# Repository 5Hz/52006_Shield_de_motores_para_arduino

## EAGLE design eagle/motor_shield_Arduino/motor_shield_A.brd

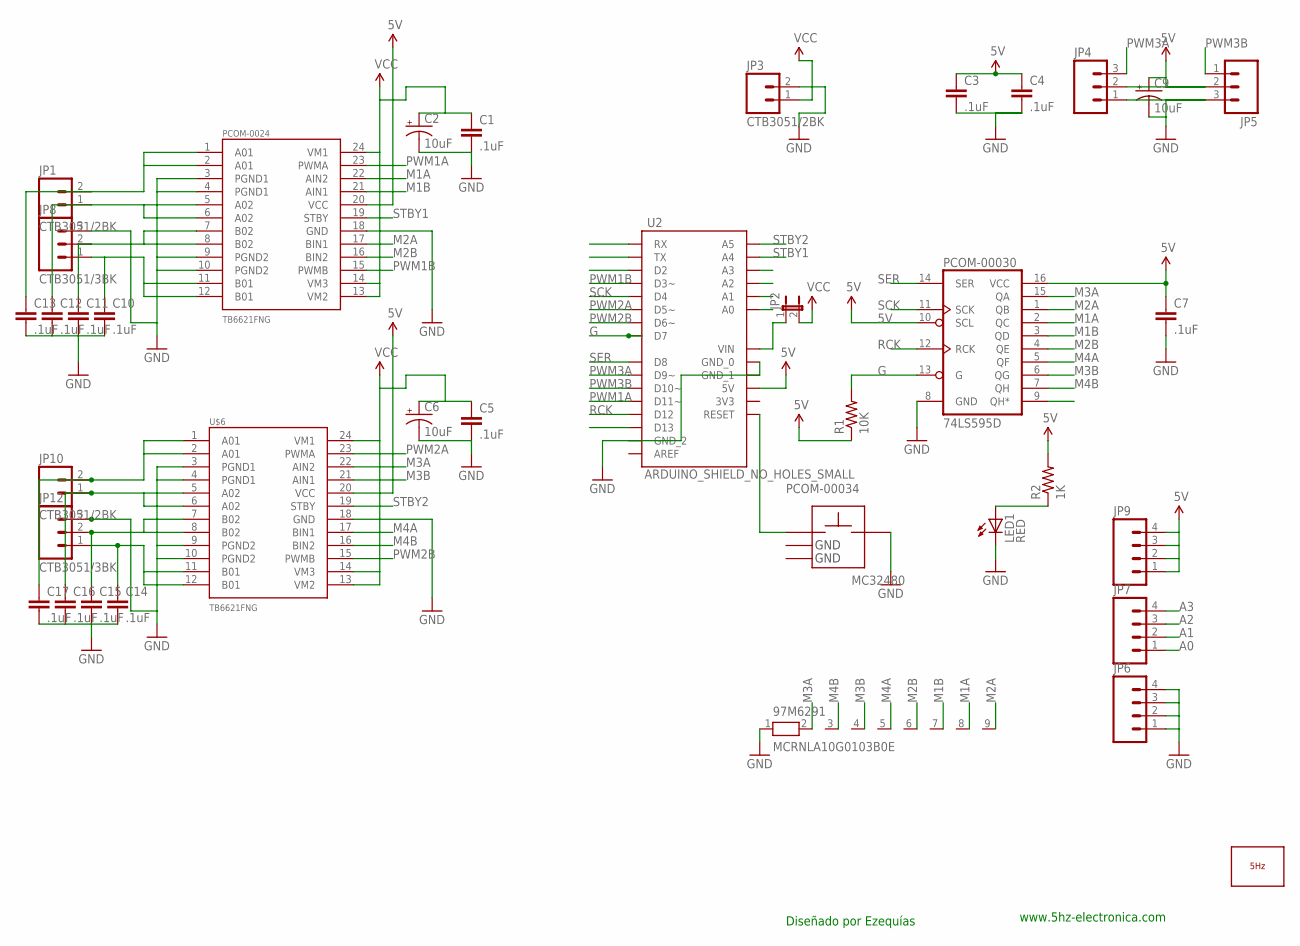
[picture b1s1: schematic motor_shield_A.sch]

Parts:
97M6291: MCRNLA10G0103B0E; RN-9
C1, C3, C4, C5, C7, C10, C11, C12, C13, C14, C15, C16, C17: .1uF; 0603-CAP
C2, C6: 10uF; EIA3528-KIT
C9: 10uF; EIA3216
JP1, JP3, JP10: CTB3051/2BK; SCREWTERMINAL-3.5MM-2
JP2: JUMPER-2PTH; 1X02
JP4, JP5: M03PTH; 1X03
JP6, JP7, JP9: M04PTH; 1X04
JP8, JP12: CTB3051/3BK; SCREWTERMINAL-3.5MM-3
LED1: RED; LED-0603
LOGO1: LOGO_5HZ_H_COOPER_10MM; 5HZ_LOGO_H_COOPER_10MM
PCOM-0024: TB6621FNG; SSOP24
PCOM-00030: 74LS595D; SO16
PCOM-00034: MC32480; MC32840
R1: 10K; 0603-RES
R2: 1K; 0603-RES
U2: ARDUINO_SHIELD_NO_HOLES_SMALL; UNO_SHIELD_SMALL_NO_HOLES
U$6: TB6621FNG; SSOP24

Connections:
5V: C3.1, C4.1, C7.1, C9.A (+), JP4.2, JP5.2, JP9.1, JP9.2, JP9.3, JP9.4, PCOM-0024.20 (VCC), PCOM-00030.10 (SCL), PCOM-00030.16 (VCC), R1.1, R2.2, U2.5V, U$6.20 (VCC)
A0: JP7.1, U2.A0
A1: JP7.2, U2.A1
A2: JP7.3, U2.A2
A3: JP7.4, U2.A3
G: PCOM-00030.13 (G), R1.2, U2.D7
GND: 97M6291.1, C1.2, C2.C (-), C3.2, C4.2, C5.2, C6.C (-), C7.2, C9.C (-), C10.2, C11.2, C12.2, C13.2, C14.2, C15.2, C16.2, C17.2, JP3.2, JP4.1, JP5.3, JP6.1, JP6.2, JP6.3, JP6.4, JP8.3, JP12.3, LED1.C, PCOM-0024.3 (PGND1), PCOM-0024.4 (PGND1), PCOM-0024.9 (PGND2), PCOM-0024.10 (PGND2), PCOM-0024.18 (GND), PCOM-00030.8 (GND), PCOM-00034.B, U2.GND_0, U2.GND_1, U2.GND_2, U$6.3 (PGND1), U$6.4 (PGND1), U$6.9 (PGND2), U$6.10 (PGND2), U$6.18 (GND)
M1A: 97M6291.8, PCOM-0024.22 (AIN2), PCOM-00030.2 (QC)
M1B: 97M6291.7, PCOM-0024.21 (AIN1), PCOM-00030.3 (QD)
M2A: 97M6291.9, PCOM-0024.17 (BIN1), PCOM-00030.1 (QB)
M2B: 97M6291.6, PCOM-0024.16 (BIN2), PCOM-00030.4 (QE)
M3A: 97M6291.2, PCOM-00030.15 (QA), U$6.22 (AIN2)
M3B: 97M6291.4, PCOM-00030.6 (QG), U$6.21 (AIN1)
M4A: 97M6291.5, PCOM-00030.5 (QF), U$6.17 (BIN1)
M4B: 97M6291.3, PCOM-00030.7 (QH), U$6.16 (BIN2)
unnamed: C13.1, JP1.2, PCOM-0024.1 (A01), PCOM-0024.2 (A01)
unnamed: C15.1, JP12.2, U$6.7 (B02), U$6.8 (B02)
unnamed: C12.1, JP1.1, PCOM-0024.5 (A02), PCOM-0024.6 (A02)
unnamed: C14.1, JP12.1, U$6.11 (B01), U$6.12 (B01)
unnamed: C11.1, JP8.2, PCOM-0024.7 (B02), PCOM-0024.8 (B02)
unnamed: JP2.1, U2.VIN
unnamed: C10.1, JP8.1, PCOM-0024.11 (B01), PCOM-0024.12 (B01)
unnamed: PCOM-00034.A@1 (A), U2.RES (RESET)
unnamed: LED1.A, R2.1
unnamed: C17.1, JP10.2, U$6.1 (A01), U$6.2 (A01)
unnamed: C16.1, JP10.1, U$6.5 (A02), U$6.6 (A02)
PWM1A: PCOM-0024.23 (PWMA), U2.D11 (D11~)
PWM1B: PCOM-0024.15 (PWMB), U2.D3 (D3~)
PWM2A: U2.D5 (D5~), U$6.23 (PWMA)
PWM2B: U2.D6 (D6~), U$6.15 (PWMB)
PWM3A: JP4.3, U2.D9 (D9~)
PWM3B: JP5.1, U2.D10 (D10~)
RCK: PCOM-00030.12 (RCK), U2.D12
SCK: PCOM-00030.11 (SCK), U2.D4
SER: PCOM-00030.14 (SER), U2.D8
STBY1: PCOM-0024.19 (STBY), U2.A4
STBY2: U2.A5, U$6.19 (STBY)
VCC: C1.1, C2.A (+), C5.1, C6.A (+), JP2.2, JP3.1, PCOM-0024.13 (VM2), PCOM-0024.14 (VM3), PCOM-0024.24 (VM1), U$6.13 (VM2), U$6.14 (VM3), U$6.24 (VM1)

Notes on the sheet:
Diseñado por Ezequías
www.5hz-electronica.com

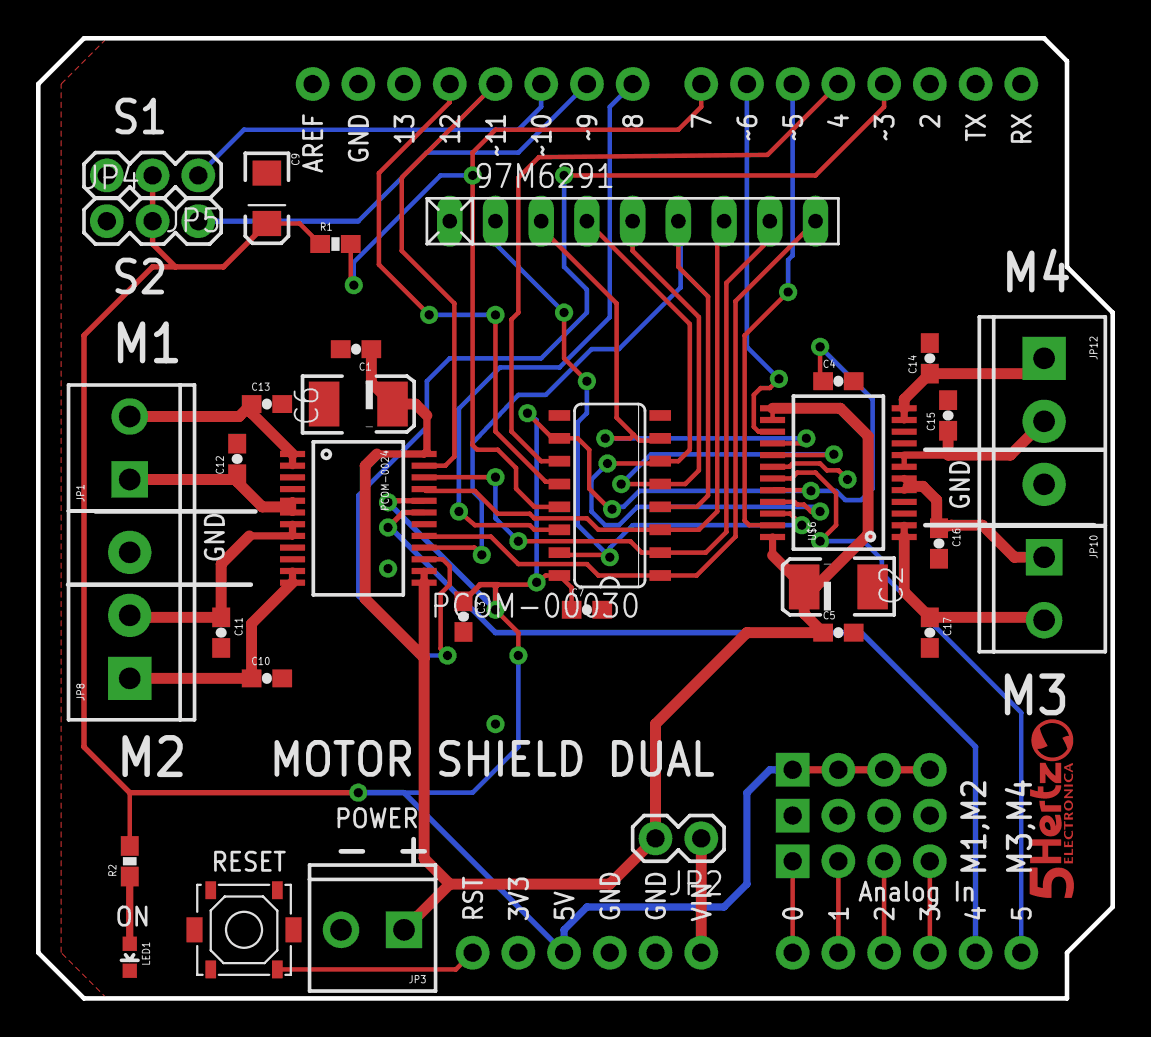
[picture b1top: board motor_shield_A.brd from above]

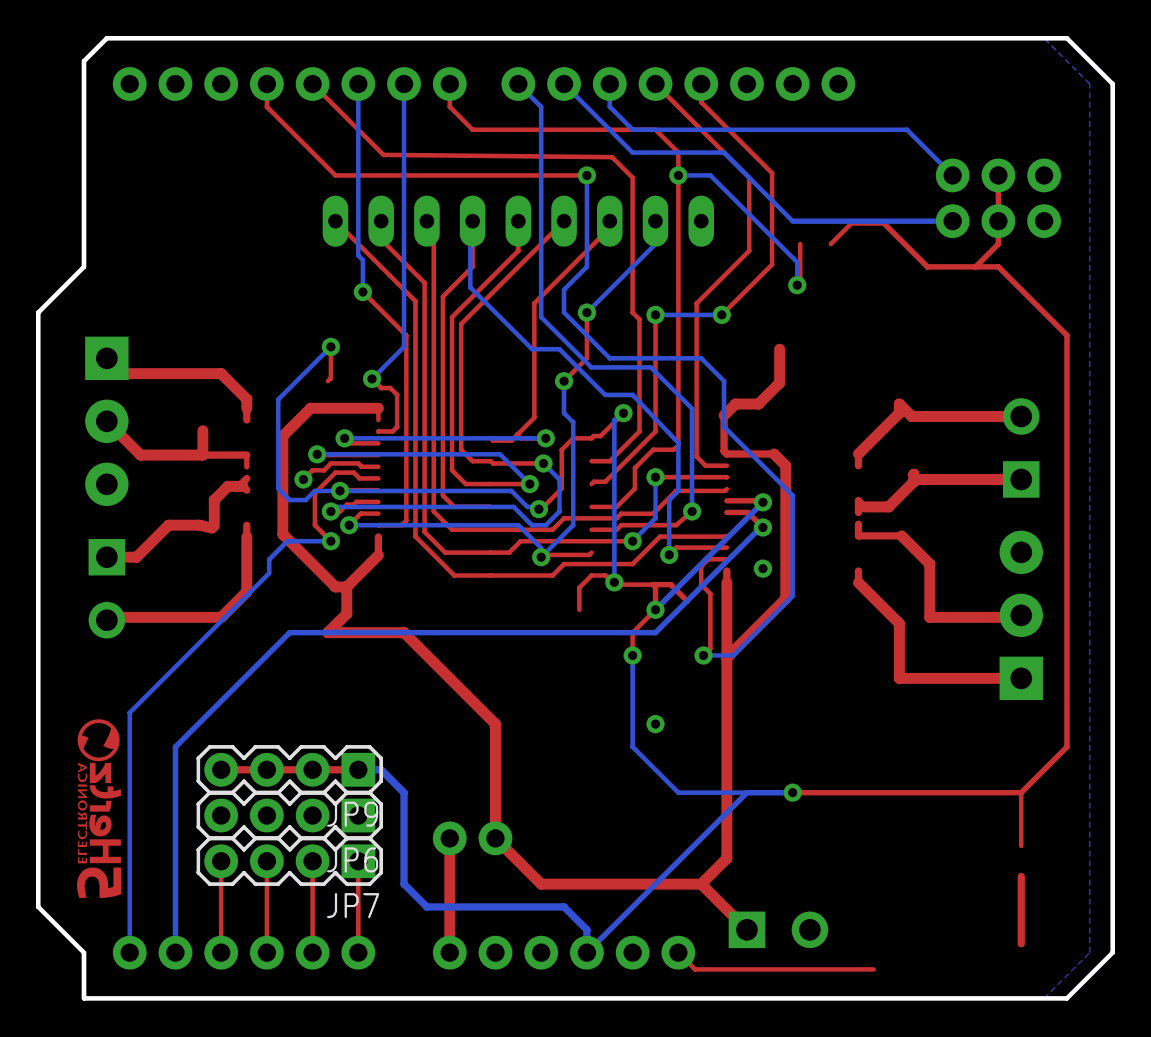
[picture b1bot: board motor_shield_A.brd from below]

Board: 2 copper layers, 59.7 x 53.3 mm, 37 parts (3 on the bottom side), 38 nets.

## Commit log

2014-01-14 creación

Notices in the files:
parts and their libraries:
SparkFun: Licensing: CC v3.0 Share-Alike You are welcome to use this library for commercial purposes.
